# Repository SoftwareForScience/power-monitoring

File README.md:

# PowerMonitoring
This project is about monitoring power usage of algorithms in a scientific setting.

## Members
 * Bram de Wit [Bram.de.wit@hva.nl](mailto:Bram.de.wit@hva.nl)
 * Mauritzio Giannattasio [Mauritzio.Giannattasio@hva.nl](Mauritzio.Giannattasio@hva.nl)
 * Stefan Schokker [Stefan.Schokker@hva.nl](mailto:Stefan.Schokker@hva.nl)

## Other links
 * [Google Drive](https://drive.google.com/drive/folders/1eERcP0KF6TMZwpRhuw7JTQKFcHHF9BiZ?usp=sharing)
 * [Trello](https://trello.com/sfspowermonitoring1)
 * [Blog](https://softwareforscience772503629.wordpress.com/blog-feed/)

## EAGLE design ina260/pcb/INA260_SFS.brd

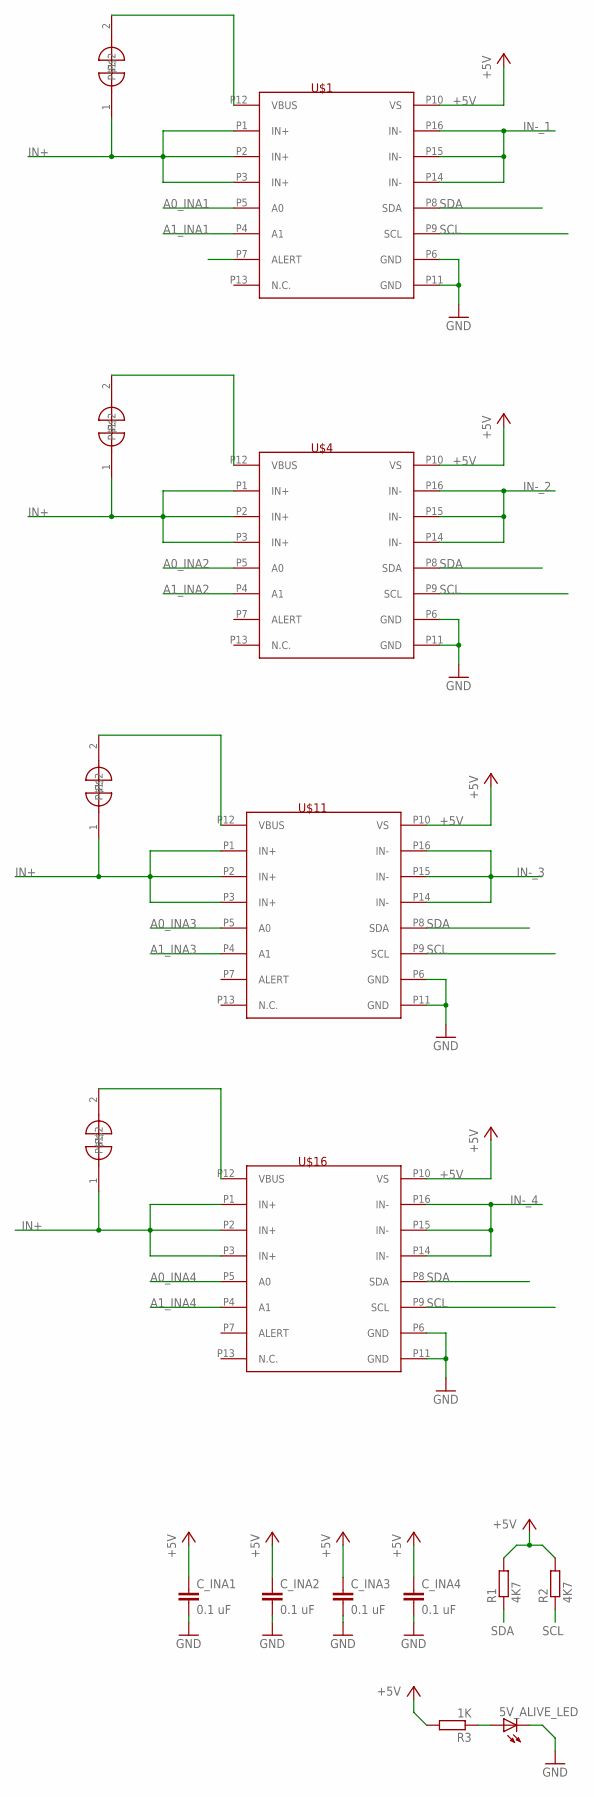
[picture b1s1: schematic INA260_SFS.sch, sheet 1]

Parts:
5V_ALIVE_LED: LEDSMT1206; 1206
C_INA1, C_INA2, C_INA3, C_INA4: 0.1 uF; RESC0805_N
R1, R2: 4K7; M0805
R3: 1K; M0805
U$1, U$4, U$11, U$16: INA260; TSSOP16L
U$5, U$6, U$12, U$17: CLOSEDJUMPER; SOLDERJUMPER_CLOSEDWIRE

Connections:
+5V: C_INA1.1, C_INA2.1, C_INA3.1, C_INA4.1, R1.2, R2.2, R3.2, U$1.P10 (VS), U$4.P10 (VS), U$11.P10 (VS), U$16.P10 (VS); also elsewhere on the board
A0_INA1: U$1.P5 (A0); also elsewhere on the board
A0_INA2: U$4.P5 (A0); also elsewhere on the board
A0_INA3: U$11.P5 (A0); also elsewhere on the board
A0_INA4: U$16.P5 (A0); also elsewhere on the board
A1_INA1: U$1.P4 (A1); also elsewhere on the board
A1_INA2: U$4.P4 (A1); also elsewhere on the board
A1_INA3: U$11.P4 (A1); also elsewhere on the board
A1_INA4: U$16.P4 (A1); also elsewhere on the board
GND: 5V_ALIVE_LED.C, C_INA1.2, C_INA2.2, C_INA3.2, C_INA4.2, U$1.P6 (GND), U$1.P11 (GND), U$4.P6 (GND), U$4.P11 (GND), U$11.P6 (GND), U$11.P11 (GND), U$16.P6 (GND), U$16.P11 (GND); also elsewhere on the board
IN+: U$1.P1 (IN+), U$1.P2 (IN+), U$1.P3 (IN+), U$4.P1 (IN+), U$4.P2 (IN+), U$4.P3 (IN+), U$5.1, U$6.1, U$11.P1 (IN+), U$11.P2 (IN+), U$11.P3 (IN+), U$12.1, U$16.P1 (IN+), U$16.P2 (IN+), U$16.P3 (IN+), U$17.1; also elsewhere on the board
IN-_1: U$1.P14 (IN-), U$1.P15 (IN-), U$1.P16 (IN-); also elsewhere on the board
IN-_2: U$4.P14 (IN-), U$4.P15 (IN-), U$4.P16 (IN-); also elsewhere on the board
IN-_3: U$11.P14 (IN-), U$11.P15 (IN-), U$11.P16 (IN-); also elsewhere on the board
IN-_4: U$16.P14 (IN-), U$16.P15 (IN-), U$16.P16 (IN-); also elsewhere on the board
unnamed: U$1.P12 (VBUS), U$6.2
unnamed: 5V_ALIVE_LED.A, R3.1
unnamed: U$4.P12 (VBUS), U$5.2
unnamed: U$11.P12 (VBUS), U$12.2
unnamed: U$16.P12 (VBUS), U$17.2
SCL: R2.1, U$1.P9 (SCL), U$4.P9 (SCL), U$11.P9 (SCL), U$16.P9 (SCL); also elsewhere on the board
SDA: R1.1, U$1.P8 (SDA), U$4.P8 (SDA), U$11.P8 (SDA), U$16.P8 (SDA); also elsewhere on the board

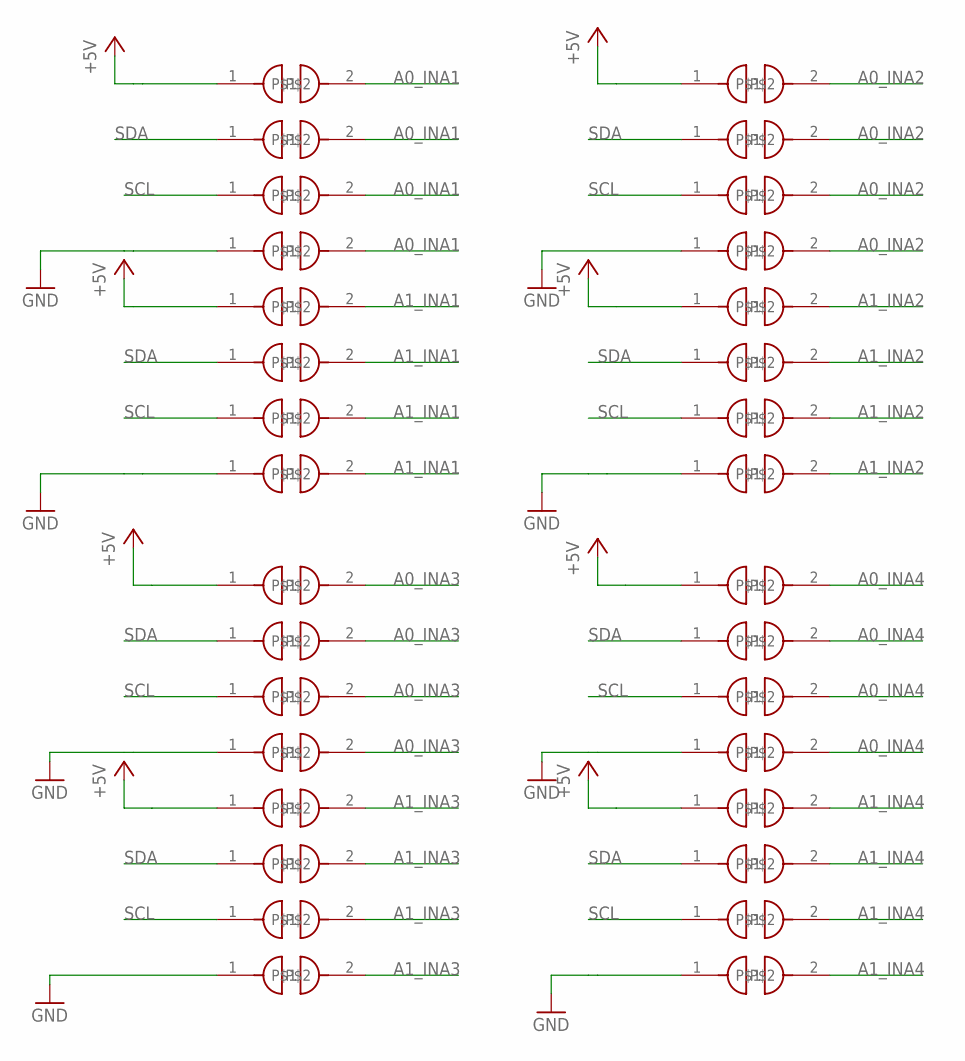
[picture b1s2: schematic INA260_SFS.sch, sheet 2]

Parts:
U$38, U$39, U$40, U$41, U$42, U$43, U$44, U$45, U$46, U$47, U$48, U$49, U$50, U$51, U$52, U$53, U$54, U$55, U$56, U$57, U$58, U$59, U$60, U$61, U$62, U$63, U$64, U$65, U$66, U$67, U$68, U$69: JUMPER; SOLDERJUMPER_ARROW_NOPASTE

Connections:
+5V: U$41.1, U$45.1, U$49.1, U$53.1, U$57.1, U$61.1, U$65.1, U$69.1; also elsewhere on the board
A0_INA1: U$42.2, U$43.2, U$44.2, U$45.2; also elsewhere on the board
A0_INA2: U$50.2, U$51.2, U$52.2, U$53.2; also elsewhere on the board
A0_INA3: U$58.2, U$59.2, U$60.2, U$61.2; also elsewhere on the board
A0_INA4: U$66.2, U$67.2, U$68.2, U$69.2; also elsewhere on the board
A1_INA1: U$38.2, U$39.2, U$40.2, U$41.2; also elsewhere on the board
A1_INA2: U$46.2, U$47.2, U$48.2, U$49.2; also elsewhere on the board
A1_INA3: U$54.2, U$55.2, U$56.2, U$57.2; also elsewhere on the board
A1_INA4: U$62.2, U$63.2, U$64.2, U$65.2; also elsewhere on the board
GND: U$38.1, U$42.1, U$46.1, U$50.1, U$54.1, U$58.1, U$62.1, U$66.1; also elsewhere on the board
SCL: U$39.1, U$43.1, U$47.1, U$51.1, U$55.1, U$59.1, U$63.1, U$67.1; also elsewhere on the board
SDA: U$40.1, U$44.1, U$48.1, U$52.1, U$56.1, U$60.1, U$64.1, U$68.1; also elsewhere on the board

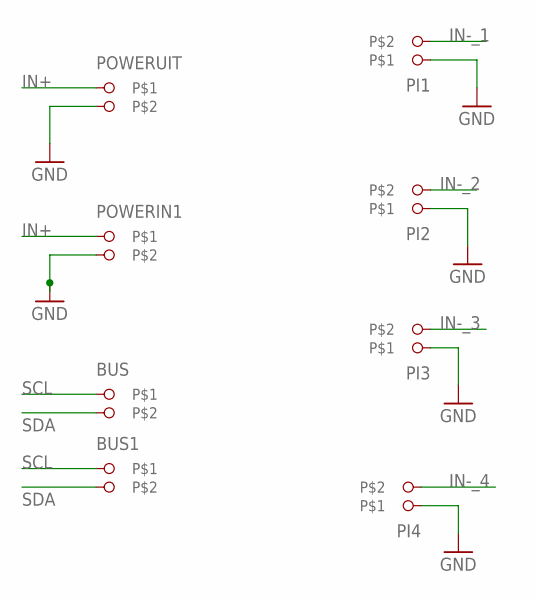
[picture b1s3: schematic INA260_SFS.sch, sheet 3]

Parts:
BUS, BUS1: CON_3.81MM2_SIDE; CON_3.81MM2
PI1, PI2, PI3, PI4: CON_3.81MM2_SIDE; CON_3.81MM2
POWERIN1: CON_3.81MM2_SIDE; CON_3.81MM2
POWERUIT: CON_3.81MM2_SIDE; CON_3.81MM2

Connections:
GND: PI1.P$1, PI2.P$1, PI3.P$1, PI4.P$1, POWERIN1.P$2, POWERUIT.P$2; also elsewhere on the board
IN+: POWERIN1.P$1, POWERUIT.P$1; also elsewhere on the board
IN-_1: PI1.P$2; also elsewhere on the board
IN-_2: PI2.P$2; also elsewhere on the board
IN-_3: PI3.P$2; also elsewhere on the board
IN-_4: PI4.P$2; also elsewhere on the board
SCL: BUS.P$1, BUS1.P$1; also elsewhere on the board
SDA: BUS.P$2, BUS1.P$2; also elsewhere on the board

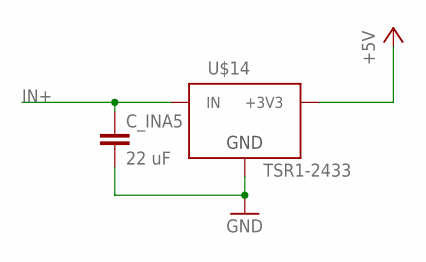
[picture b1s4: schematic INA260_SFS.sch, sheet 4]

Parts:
C_INA5: 22 uF; RESC0805_N
U$14: TSR1-2433; TSR-1

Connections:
+5V: U$14.3 (+3V3); also elsewhere on the board
GND: C_INA5.2, U$14.2 (GND); also elsewhere on the board
IN+: C_INA5.1, U$14.1 (IN); also elsewhere on the board

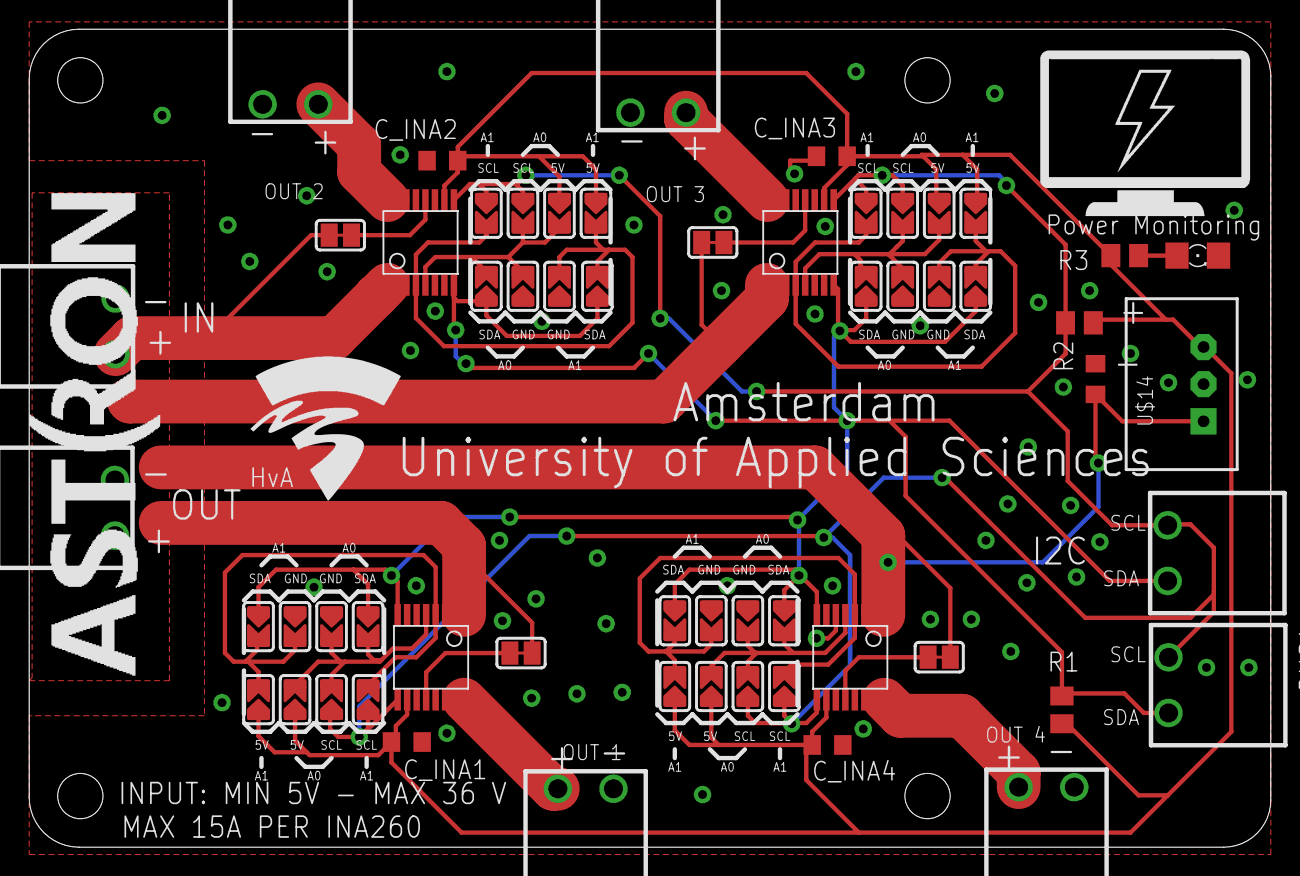
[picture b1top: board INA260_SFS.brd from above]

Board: 2 copper layers, 85.0 x 56.0 mm, 66 parts (1 on the bottom side), 22 nets.

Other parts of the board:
U$2: POWER_MONITORING_LOGO
U$3, U$7, U$8, U$9: JUMPER_INFO
U$10: HVA_LOGO
U$13: ASTRON_LOGO
U$15: ED_KLEIN

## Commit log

2018-12-06 Visualisation - Basics
    No visualisation yet, only the gathering of data
2019-01-10 Restoring commit + Monasca
2019-01-10 removed weird file
2019-01-10 Ansible
2019-01-10 After rebase, cleaned directories
2019-01-17 monasca agent update
2019-01-22 Git pull with ansible
2019-01-22 make RPI ready4use with ansible
2019-01-23 Install dependencies RPI with ansible
2019-01-29 Rewritten filter and metric to Prometheus standard
2019-01-29 fixed typo
2019-01-29 InstallDeb fixes
2019-01-29 removed unnecessary python module
2019-01-29 oke laatste
2019-01-29 oke allerlaatste
2019-01-29 oke aller-aller-laatste (todo: code coverage)
2019-01-29 allerlaatste met typo
2019-01-29 hoooi
2019-01-29 test
2019-01-29 huhuhu
2019-01-29 gefixt
2019-01-29 power metrics working, metric modules changed, filter working
2019-01-29 prometheus fix
2019-01-30 StopServices made
2019-01-30 Ansible runs programs in background, Ansible kills services
2019-01-31 added psutil with cpu/ram
2019-03-01 Add CHANGELOG
2019-03-01 Add README.md
2019-03-01 Add CONTRIBUTING
2019-03-01 Add new file
2019-03-01 Trigger New Webhook
2019-03-01 Update trigger
2019-03-15 Add 'git@github.com:Astron-Power-Monitoring/Visualisation.git/' from commit 'd2938db215ae5c5c7f0d607a58c54de4e53cc4d2'
    git-subtree-dir: git@github.com:Astron-Power-Monitoring/Visualisation.git
    git-subtree-mainline: d2938db215ae5c5c7f0d607a58c54de4e53cc4d2
    git-subtree-split: d2938db215ae5c5c7f0d607a58c54de4e53cc4d2
2019-03-15 remove wrong subtree add
2019-03-15 removed .idea
2019-03-21 added documantation team 2018
2019-03-21 spelling correction
2019-03-21 Hope this is working...
2019-03-21 Ahhhh, Some basic setup you know?
2019-03-21 added ssh files
2019-03-21 Added some genious init.sh HAHA
2019-03-21 Little mistake, don't blame me, blame my keyboard
2019-03-21 Another mistake, ahh, it's late..
2019-03-21 Git install needed in init.sh
2019-03-21 Sooo, let's check if it works now..., and else, create some issues...
2019-03-21 Fixes some things for install script to complete..., like creating the docker-image dir with Dockerfile
2019-03-21 Some bugfixes and a better DNS fix (permanent fix)
2019-03-21 updated multi-cluster script
2019-03-21 Added docker-cluster as submodule
2019-03-21 Updated submodule (docker-cluster)
2019-03-22 Update README.md (changed link to image)
2019-03-25 WIP new setup
2019-03-25 Updated setup (first reboot required??)
2019-03-25 Back 1 setup file
2019-03-25 Bug found.. stupid tutorial of docker cluster is wrong!
2019-03-25 removed error making files..
2019-03-25 no longer needed override.conf
2019-03-28 Update setup.sh -> swarp setup
2019-03-28 Update setup.sh -> sudo
2019-03-28 Update README.md (trigger)
2019-03-28 Remove trigger
2019-04-04 removed submodule
2019-04-04 Squashed 'docker-cluster/' content from commit 94519c1
    git-subtree-dir: docker-cluster
    git-subtree-split: 94519c14228b461c8d6989c3d7105b44c7215fd0
2019-04-04 remove subtree without commits
2019-04-04 Update README.md (remove trigger)
2019-04-04 Added .gitignore
2019-05-15 Initial commit -> default docker-compose metricbeats setup for ARM
2019-05-15 First commit of working version
2019-06-10 testv1
2019-06-10 testv2 - working partial (without boxes)
2019-06-10 Added models, labels and examples
2019-06-11 Working with prometheus
2019-06-12 Basic python Dockerfile
2019-06-12 Add requirements.txt
2019-06-12 Edited Docker stack to fit our needs
2019-06-12 Small tmp update
2019-06-12 Working metricbeat build
2019-06-12 Changed image to registry image
2019-06-12 Working DockerFile
2019-06-12 Fix broken file?
2019-06-12 Fix more files
2019-06-12 Make example
2019-06-12 Gitignore additions
2019-06-12 Correct folder for scripts
2019-06-12 Working now!
2019-06-12 working
2019-06-13 Final changes
2019-06-14 Reordered repo
2019-06-14 WIP reorder
2019-06-14 Added all subrepos as submodule
2019-06-19 New version of Readme
2019-06-19 Fix titles in readme
2019-06-19 Typo
2019-06-20 Added CI
2019-06-20 Update Dockerfile
2019-06-22 Updated subrepos
2019-06-22 Add new directory
2019-06-22 Upload New File
2019-09-30 Added link to wordpress blog
2019-10-17 intial version, only setups and closes INA device, untested
2019-10-17 Algorime case
    a small paper on what algorithm we should choose for our case study
2019-10-25 First layout pcb
2019-10-25 finshed first design. after review ready for order
2019-10-25 added silkscreen layer pcb
    logos added and descriptions of terminals
    also added i2c pullups and alive LED
2019-10-28 3.3 volt dc/dc converter
2019-10-28 added I2C second bus line terminal
2019-10-31 Least check before order
2019-10-31 misplaced names corectted on this version
2019-11-07 ZIP file for jlc order
    the zip file that was used to order the pcb's if new ones are needed this file can be used
2019-11-13 first draft for server client set up .cpp
2019-11-13 Able to read current, voltage and power from the INA260's
2019-11-13 paper on algorithm further expanded
    research on fft explanation of how the fourier transform works and how we want to setup the test
2019-11-14 Started FFT code and end of day push
    paper research done start with code now
2019-11-15 non modulair server client temp set up working. Starting now on modulair setup.
2019-11-15 working non moduliar version.
2019-11-15 can now read hosts and i2c addresses from xml file
2019-11-18 segment error in server side remains after a large number of calls from the client. Client side needs to be commented and names need to be updated and map
2019-11-18 Image processing works
    Can make BMP from string and convert this to the freq domain and back.
2019-11-19 now writes data (not temperature) to CSV file
2019-11-21 Cleaned up names, function return map value added
2019-11-21 Ansible playbook for FFTW installation
    added simple install method for fftw dependencies
2019-11-22 improved c++ usage, among other things
2019-11-26 trial error server
2019-11-26 fixed a memory management fault
2019-11-28 New struct added for client side to stop opening new port
2019-11-28 cleanup, added argument parser
2019-11-29 cleanup branch
2019-11-29 initial version
2019-12-03 added comments, and mpi experiment
    added some comments to fftw and mpi test
2019-12-05 Better latex file structure, added ansible playbook
2019-12-10 cleanup in preparation for merge
2019-12-10 added working libsocket server to ina260 code
2019-12-10 added silkscreen layer pcb
    logos added and descriptions of terminals
    also added i2c pullups and alive LED
2019-12-10 Removed unused gitmodules
2019-12-10 removed temperaturelogging class, now that we're server side
2019-12-10 add image to string code
2019-12-10 Retry of last commit
2019-12-11 moved documentation folder, updated docs
2019-12-11 added running section
2019-12-12 Trial run install folder Client cmake
2019-12-12 Add source code for client
2019-12-12 fftw image processing with multitrhreading
    still uses sample.h but works
2020-01-07 Added some comments
2020-01-09 Cleanup and test programs
    Cleaned up the directory and made a folder containing the test programs that can be run to test the power consumption of multi threaded FFT, multi processing FFT and multi processing mandelbrot gener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
2020-01-09 Forgot the bitmap library
    Whoops sorry
2020-01-10 Added install.yaml
2020-01-10 standard gnuplot scripts for testing
2020-01-10 update PCB silkscreen
2020-01-14 Added timer
    added a timer for the fft with multithread
2020-01-14 Update .gitmodules, again
2020-01-14 mostly fixed the install script for the logger
2020-01-14 fixed bug where the logging pi would not find it's own temperature in the map presented by the server instance
2020-01-14 updated documentation to fit fixed installer and to instruct users to edit their hosts file
2020-01-15 Add LICENSE
2020-01-16 updated client installer, moved into correct folder
2020-01-16 added installation documentation
2020-01-16 final push before push to gitlab
    everything is done except the ansible script for installation since that rely's on a github link which doesn't exist yet
2020-01-23 minor code convention, cleanup
2020-01-30 added src in ansible
    adder fftw zip
2020-01-30 move verslag into docs
2020-01-30 Ansible again
    hope it works this time
2020-01-30 Fixed documentation directory
    it's better now
2020-01-30 just making sure I don't mess up too bad
2020-01-30 for some reason the ina260 folder was in the gitignore
2020-01-30 forgot to delete a few files
2020-01-30 moved documentation
2020-01-30 fixed fftw install (maybe)
2020-01-30 minor installer fix
2020-01-30 fixed gitmodules
2020-01-30 fixed gitmodules, again
